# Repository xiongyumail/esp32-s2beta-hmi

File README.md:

# _ESP32-S2Beta-HMI_

_HMI evaluation suite for new low power, low cost and secure Internet of Things chip ESP32-S2. ESP32-S2 chip is equipped with Xtensa 32-bit LX7 single-core processor.
Working frequency up to 240 MHz, providing a wealth of peripheral interfaces, including SPI, I2S, UART, I2C, LED PWM, PCNT, LCD interface, Camera interface, ADC, DAC,
Touch sensors, temperature sensors and up to 43 GPIOs. Supports high-resolution LCD displays and Camera Sensor, as well as a variety of extension options.
Perfectly supports open source GUI LittleVGL, providing a large number of rich and easy-to-use GUI components and design examples._

* Development board Structure

  * High Definition Resolution: 800x480 4.3 inch

  * Multiple interfaces: 8080, 6800, SPI

  * Easy to use and beautiful GUI: LittleVGL

  * Powerful and rich graphics components: buttons, charts, lists, sliders, images, etc.

  * A large number of sensor drivers: WS2812, MPU6050, HTS221, BH170, ES8311, OV2640 etc.

  * Multiple GUI examples: RGB LED Color picker, MPU6050 Data Curve, A simple piano, Simple Terminal, etc.

## Contents

* Directory tree

    ```
    ├── add_path.sh
    ├── docs
    ├── projects
    │   └── hmi
    ├── README.md
    └── tools
        ├── esp-idf
        └── xtensa-esp32s2-elf
    ```

    * projects

      Development examples

    * tools

      * ESP32-S2 sdk

      * ESP32-S2 toolchain

    * Data

      * Schematic diagram

      * Misc

## How to use

You can follow the steps below to set up the development environment, or directly download the release version of the full environment.

* clone

  ```bash
  git clone --recursive https://gitlab.espressif.cn:6688/yxiong/esp32-s2beta-hmi
  cd esp32-s2beta-hmi
  ```

  * note

    Don't omit `--recursive`, because we use submodule.

* update

  ```bash
  git pull
  git submodule update --init --recursive
  ```

* Install toolchain

  ```bash
  ./tools/esp-idf/install.sh
  . ./tools/esp-idf/export.sh
  ```

* Add environment variables

  ```bash
  . add_path.sh
  ```
  * note

    Don't omit `"."`

## Appendix

### Schematic

* [Main Board](docs/SCH_ESP32-S2-HMI_V1_20190528A.pdf)

* [LCD Board](docs/SCH_ESP32-S2-HMI-LCD_V1_0_20190611A.pdf)

* [Audio Board](docs/audio.pdf)

* [Touch Board](docs/TOUCH.pdf)

### Datasheet

* [ESP32-S2](docs/esp32-s2_datasheet_en.pdf)

* [LCD-NT35510](docs/LCD_NT35510.pdf)

* [CAM-OV2640](docs/LCD_NT35510.pdf)

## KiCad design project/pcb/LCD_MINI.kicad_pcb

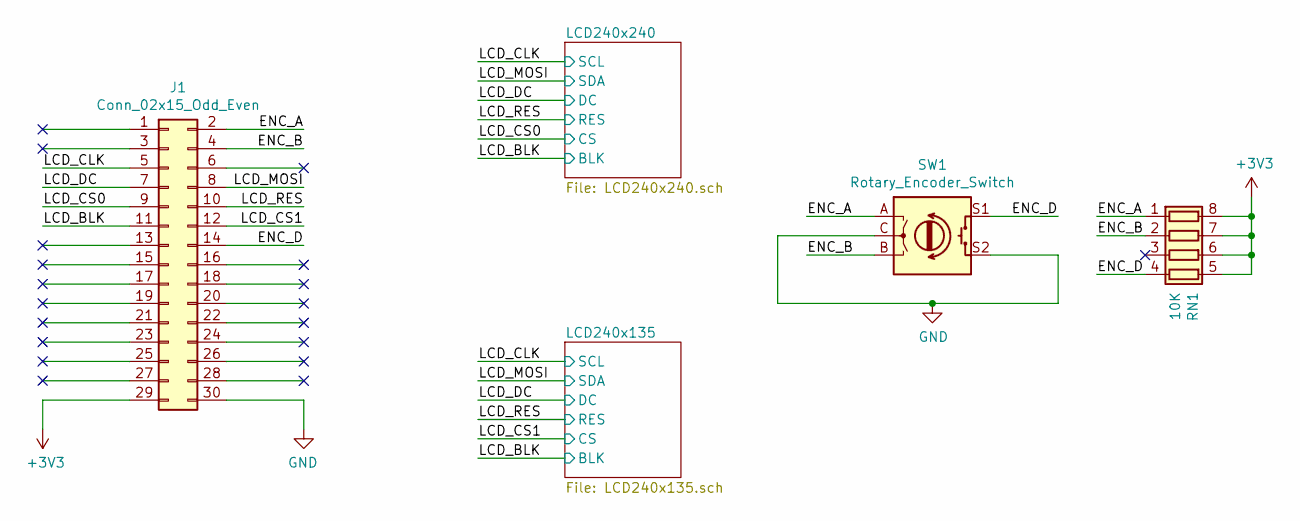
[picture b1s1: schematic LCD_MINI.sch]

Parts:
J1: Conn_02x15_Odd_Even; PinHeader_2x15_P2.54mm_Vertical
RN1: 10K; R_Array_Concave_4x0402
SW1: Rotary_Encoder_Switch; RotaryEncoder_Alps_EC11E-Switch_Vertical_H20mm

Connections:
+3V3: J1.29, RN1.5 (R4.2), RN1.6 (R3.2), RN1.7 (R2.2), RN1.8 (R1.2); also elsewhere on the board
/ENC_A: J1.2, RN1.1 (R1.1), SW1.A
/ENC_B: J1.4, RN1.2 (R2.1), SW1.B
/ENC_D: J1.14, RN1.4 (R4.1), SW1.S1
/LCD_BLK: J1.11; also elsewhere on the board
/LCD_CLK: J1.5; also elsewhere on the board
/LCD_CS0: J1.9; also elsewhere on the board
/LCD_CS1: J1.12; also elsewhere on the board
/LCD_DC: J1.7; also elsewhere on the board
/LCD_MOSI: J1.8; also elsewhere on the board
/LCD_RES: J1.10; also elsewhere on the board
GND: J1.30, SW1.C, SW1.S2; also elsewhere on the board

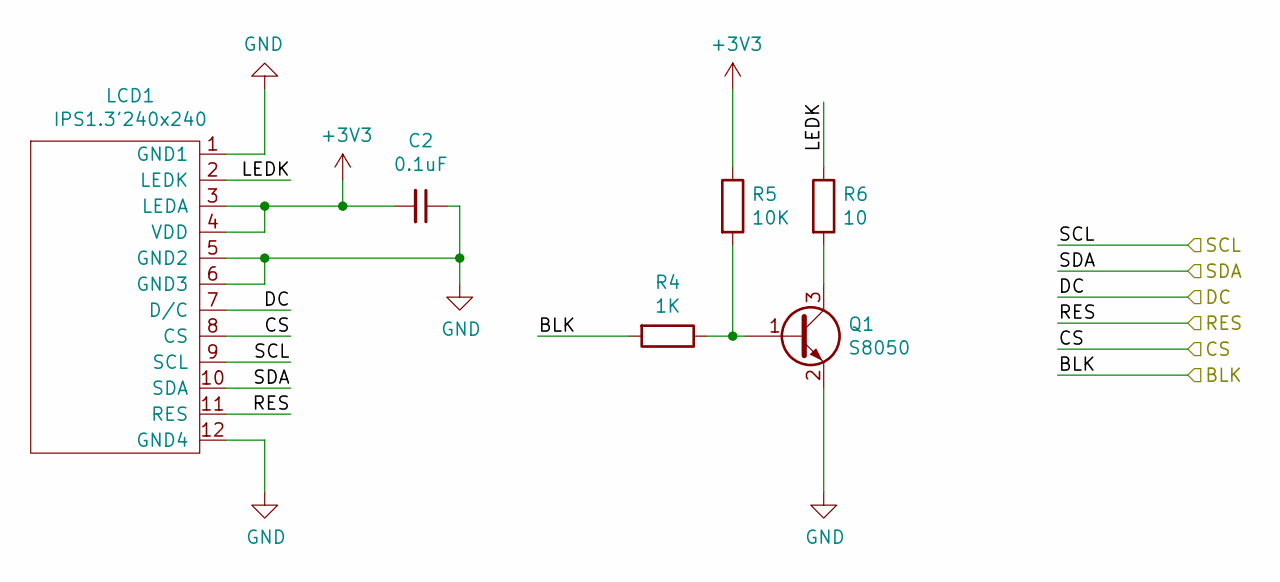
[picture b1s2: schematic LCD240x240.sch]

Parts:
C2: 0.1uF; C_0402_1005Metric
LCD1: IPS1.3'240x240
Q1: S8050; SOT-23
R4: 1K; R_0402_1005Metric
R5: 10K; R_0402_1005Metric
R6: 10; R_0402_1005Metric

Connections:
+3V3: C2.2, LCD1.3 (LEDA), LCD1.4 (VDD), R5.1; also elsewhere on the board
/LCD240x240/LEDK: LCD1.2 (LEDK), R6.1
/LCD_BLK: R4.2; also elsewhere on the board
/LCD_CLK: LCD1.9 (SCL); also elsewhere on the board
/LCD_CS0: LCD1.8 (CS); also elsewhere on the board
/LCD_DC: LCD1.7 (D/C); also elsewhere on the board
/LCD_MOSI: LCD1.10 (SDA); also elsewhere on the board
/LCD_RES: LCD1.11 (RES); also elsewhere on the board
GND: C2.1, LCD1.1 (GND1), LCD1.5 (GND2), LCD1.6 (GND3), LCD1.12 (GND4), Q1.2 (E); also elsewhere on the board
unnamed: Q1.1 (B), R4.1, R5.2
unnamed: Q1.3 (C), R6.2

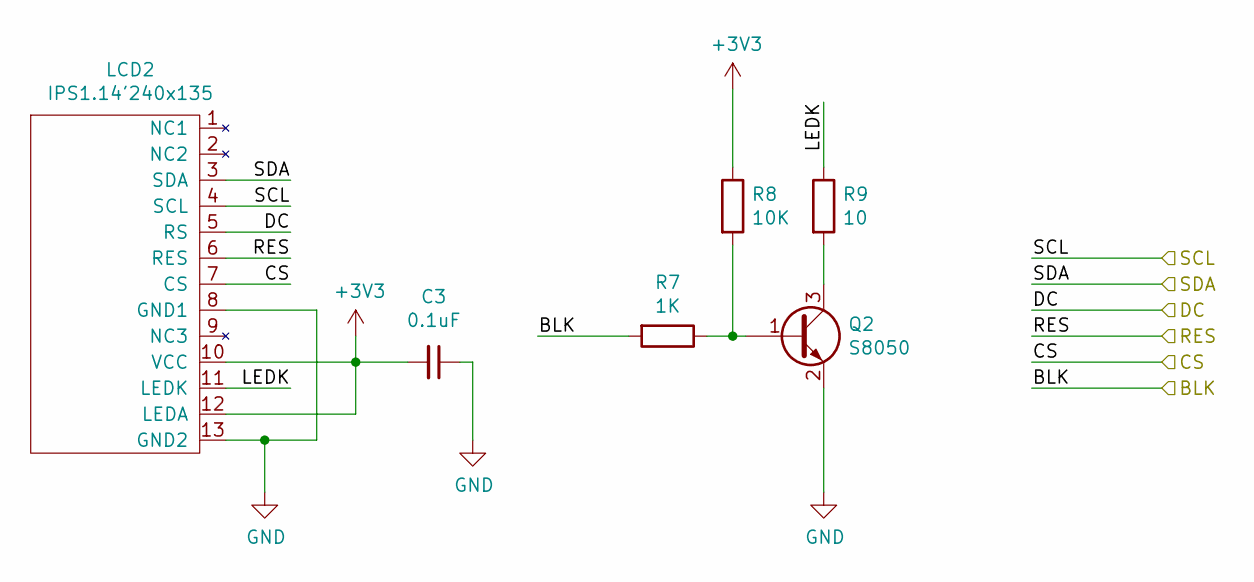
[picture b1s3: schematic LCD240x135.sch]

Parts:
C3: 0.1uF; C_0402_1005Metric
LCD2: IPS1.14'240x135
Q2: S8050; SOT-23
R7: 1K; R_0402_1005Metric
R8: 10K; R_0402_1005Metric
R9: 10; R_0402_1005Metric

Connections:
+3V3: C3.2, LCD2.10 (VCC), LCD2.12 (LEDA), R8.1; also elsewhere on the board
/LCD240x135/LEDK: LCD2.11 (LEDK), R9.1
/LCD_BLK: R7.2; also elsewhere on the board
/LCD_CLK: LCD2.4 (SCL); also elsewhere on the board
/LCD_CS1: LCD2.7 (CS); also elsewhere on the board
/LCD_DC: LCD2.5 (RS); also elsewhere on the board
/LCD_MOSI: LCD2.3 (SDA); also elsewhere on the board
/LCD_RES: LCD2.6 (RES); also elsewhere on the board
GND: C3.1, LCD2.8 (GND1), LCD2.13 (GND2), Q2.2 (E); also elsewhere on the board
unnamed: Q2.1 (B), R7.1, R8.2
unnamed: Q2.3 (C), R9.2

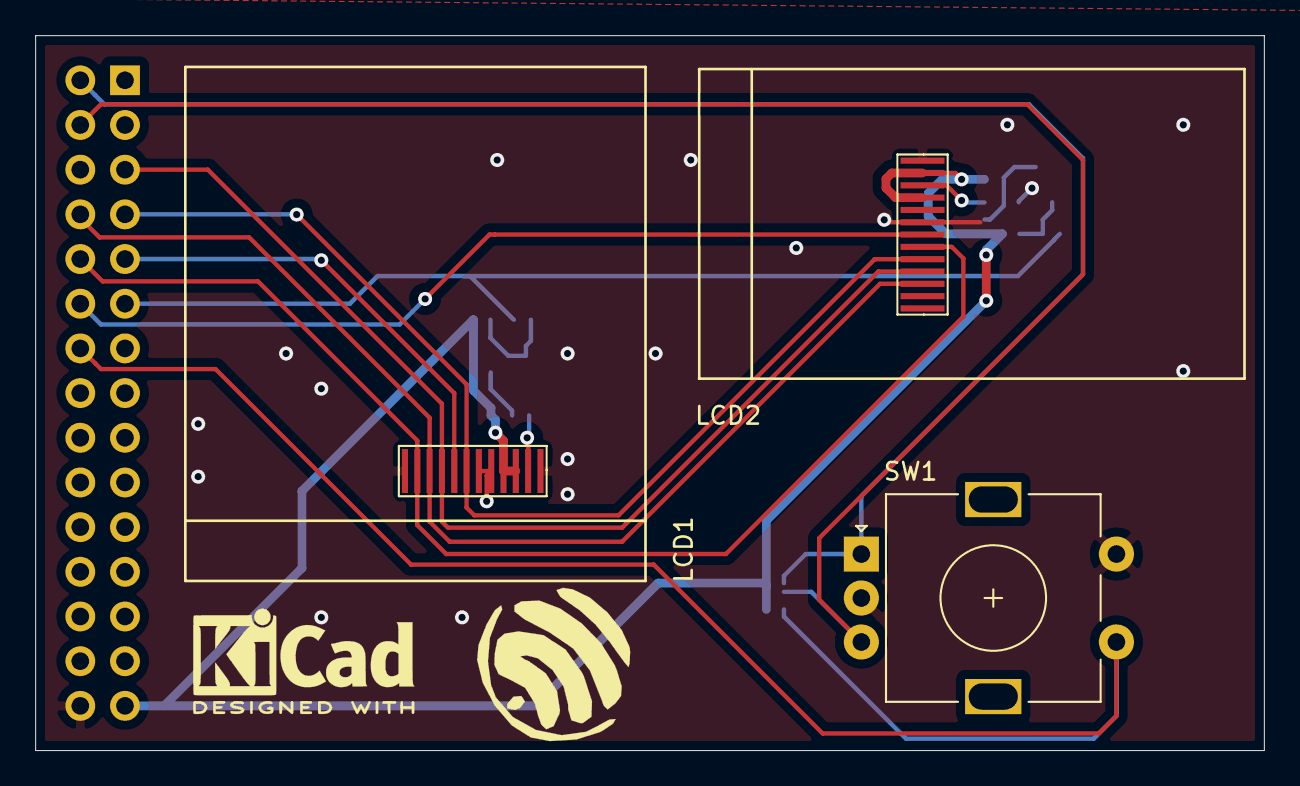
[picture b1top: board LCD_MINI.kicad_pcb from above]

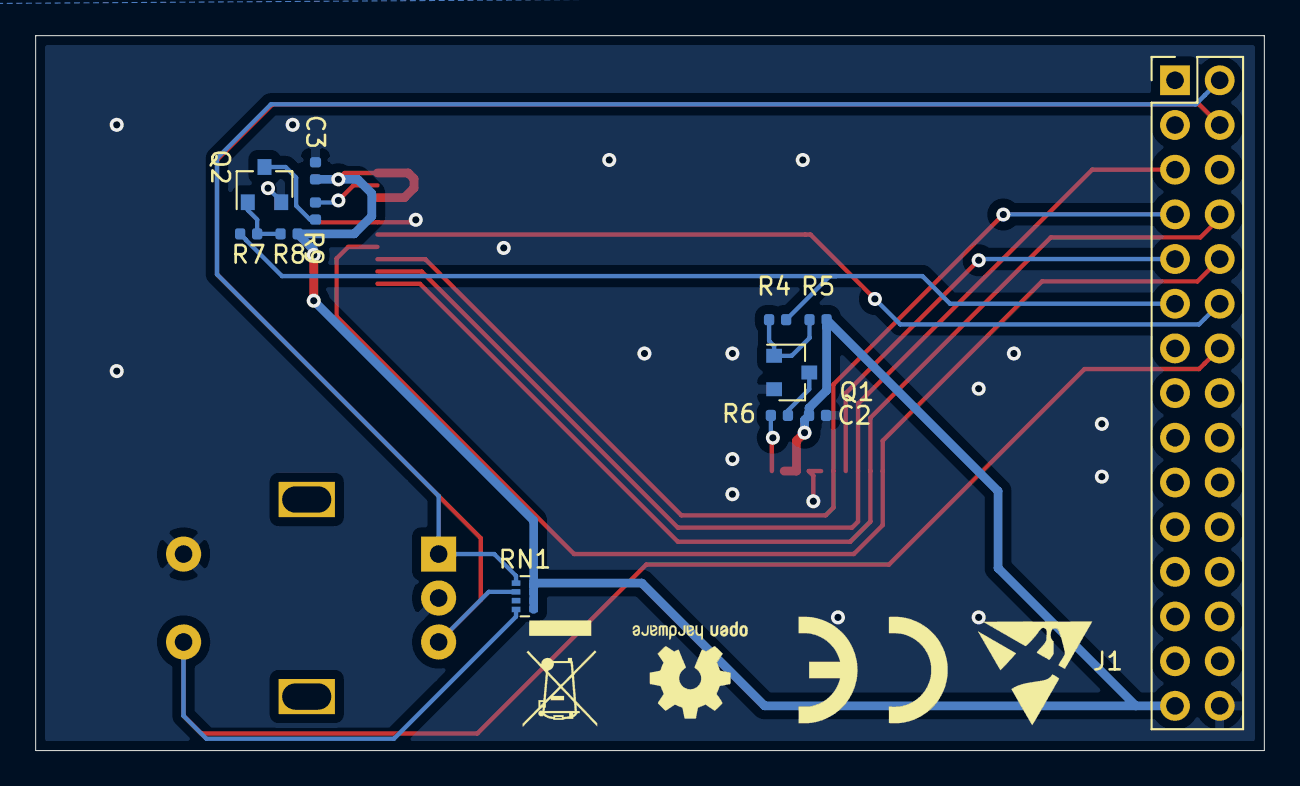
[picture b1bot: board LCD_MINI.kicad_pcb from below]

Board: 2 copper layers, 69.9 x 40.6 mm, 15 parts (12 on the bottom side), 18 nets.

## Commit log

2019-06-18 i2c ok
2019-06-18 bh1750 ok
2019-06-19 lcd ok
2019-06-20 touch ok
2019-06-21 test
2019-06-24 simple ok
2019-06-24 canvas test
2019-06-25 color_picker ok
2019-06-25 led ok
2019-06-25 rmt ok
2019-07-01 wifi test ok
2019-07-05 lvgl v6.0
2019-07-08 audio ok
2019-07-09 sntp ok
2019-07-10 udp ok
2019-07-10 move project
2019-07-10 add audio
2019-07-10 change flash size
2019-07-11 piano ok
2019-07-11 hmi ok
2019-07-29 feature(audio): add touch function
2019-07-29 add kconfig
2019-08-09 add pcb
2019-08-13 bin ok
2019-08-14 camera and lcd ok
2019-08-15 test esp_camera
2019-08-21 camera ok
2019-08-21 update lcd
2019-08-21 audio add led
2019-08-27 add led
2019-08-27 master update
2019-08-27 update master
2019-09-05 cam case ok
2019-10-15 lcd 8 bit ok
2019-10-15 lcd cam ok
2019-10-15 lcd cam demo
2019-11-01 clean project
2019-11-01 sccb ok
2019-11-01 fix readme
2019-11-19 update esp-idf
2019-11-27 add lua
2019-11-29 lua ok
2019-11-30 fix some problem
2019-12-03 esp lua support linenoise
2019-12-03 sdkconfig
2020-02-21 memory test
2020-02-22 ring dma test ok
2020-02-23 add lcd_write_data
2020-02-24 good than before
2020-03-14 refactor test
